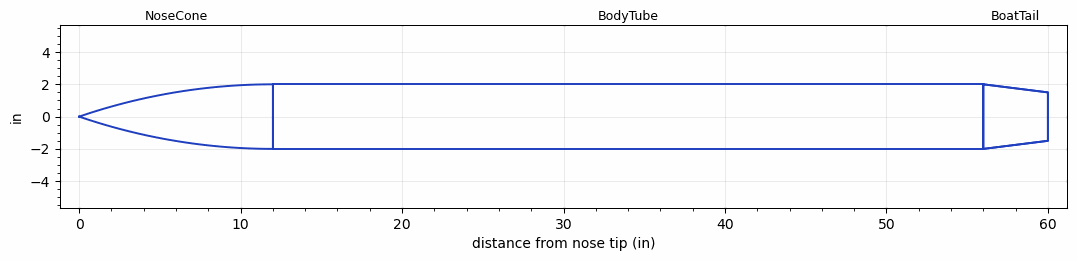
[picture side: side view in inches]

<RASAeroDocument>
 <FileVersion>2</FileVersion>
 <RocketDesign>
  <NoseCone>
   <Length>12</Length>
   <Diameter>4</Diameter>
   <Shape>Tangent Ogive</Shape>
   <Location>0</Location>
  </NoseCone>
  <BodyTube>
   <Length>44</Length>
   <Diameter>4</Diameter>
   <Location>12</Location>
   <BoattailLength>4</BoattailLength>
   <BoattailRearDiameter>3</BoattailRearDiameter>
  </BodyTube>
  <BoatTail>
   <Length>4</Length>
   <Diameter>4</Diameter>
   <RearDiameter>3</RearDiameter>
   <Location>56</Location>
  </BoatTail>
  <Surface>Smooth (Zero Roughness)</Surface>
  <ModifiedBarrowman>False</ModifiedBarrowman>
  <Turbulence>True</Turbulence>
  <UseBooster1>False</UseBooster1>
  <UseBooster2>False</UseBooster2>
  <Comments>Afterbody component study A-boattail</Comments>
 </RocketDesign>
 <LaunchSite>
  <Altitude>0</Altitude>
  <Pressure>29.9214</Pressure>
  <RodAngle>0</RodAngle>
  <RodLength>6.5617</RodLength>
  <Temperature>59</Temperature>
  <WindSpeed>0</WindSpeed>
 </LaunchSite>
 <Recovery>
  <Altitude1>656.168</Altitude1>
  <Altitude2>0</Altitude2>
  <DeviceType1>Parachute</DeviceType1>
  <DeviceType2>None</DeviceType2>
  <Event1>True</Event1>
  <Event2>False</Event2>
  <Size1>24</Size1>
  <Size2>0</Size2>
  <EventType1>Apogee</EventType1>
  <EventType2>None</EventType2>
  <CD1>0.8</CD1>
  <CD2>0</CD2>
 </Recovery>
</RASAeroDocument>
